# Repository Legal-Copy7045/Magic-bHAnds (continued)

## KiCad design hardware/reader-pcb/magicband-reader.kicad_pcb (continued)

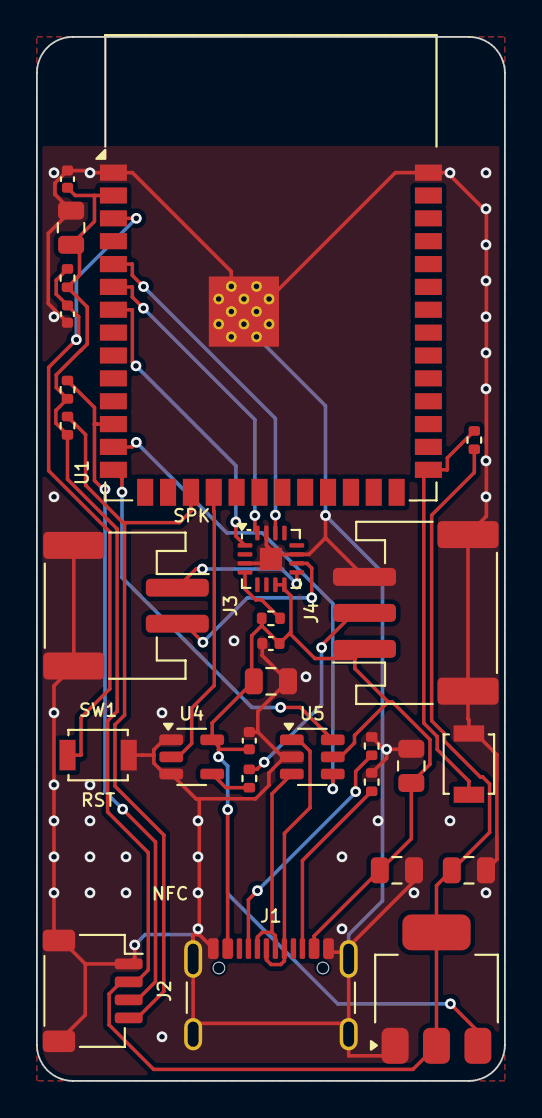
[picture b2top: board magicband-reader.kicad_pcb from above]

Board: 2 copper layers, 26.0 x 58.0 mm, 28 parts (0 on the bottom side), 22 nets.

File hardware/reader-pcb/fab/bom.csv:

Comment,Designator,Footprint,MPN,LCSC Part #
22uF,"C1,C5,C9",C_0805_2012Metric,CL21A226MAQNNNE,C45783
100nF,"C2,C7,C8",C_0402_1005Metric,CL05B104KO5NNNC,C1525
1uF,C3,C_0402_1005Metric,CL05A105KA5NQNC,C52923
10uF,"C4,C6",C_0805_2012Metric,CL21A106KAYNNNE,C15850
USB-C,J1,USB_C_Receptacle_GCT_USB4105-xx-A_16P_TopMnt_Horizontal,USB4105-GF-A,
NFC (Qwiic),J2,JST_SH_SM04B-SRSS-TB_1x04-1MP_P1.00mm_Horizontal,SM04B-SRSS-TB(LF)(SN),
Speaker,J3,JST_PH_S2B-PH-SM4-TB_1x02-1MP_P2.00mm_Horizontal,S2B-PH-SM4-TB(LF)(SN),
LEDs,J4,JST_PH_S3B-PH-SM4-TB_1x03-1MP_P2.00mm_Horizontal,S3B-PH-SM4-TB(LF)(SN),
10k,"R1,R2",R_0402_1005Metric,0402WGF1002TCE,C25744
5.1k,"R3,R4",R_0402_1005Metric,0402WGF5101TCE,C25905
1M,R5,R_0402_1005Metric,0402WGF1004TCE,C26083
330R,R6,R_0402_1005Metric,0402WGF3300TCE,C25104
4.7k,"R7,R8",R_0402_1005Metric,0402WGF4701TCE,C25900
RESET,SW1,SW_SPST_B3U-1000P,B3U-1000P,
BOOT,SW2,SW_SPST_B3U-1000P,B3U-1000P,
ESP32-S3-WROOM-1-N16R8,U1,ESP32-S3-WROOM-1,ESP32-S3-WROOM-1-N16R8,C2913202
AMS1117-3.3,U2,SOT-223-3_TabPin2,AMS1117-3.3,C6186
MAX98357A,U3,TQFN-16-1EP_3x3mm_P0.5mm_EP1.23x1.23mm,MAX98357AETE+T,C910544
74AHCT1G125,U4,SOT-23-5,SN74AHCT1G125DBVR,
USBLC6-2SC6,U5,SOT-23-6,USBLC6-2SC6,C7519

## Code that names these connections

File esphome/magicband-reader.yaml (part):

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# WAV/FLAC/MP3 under 5 MB each; see docs/reader.md.
i2s_audio:
  - id: i2s_out
    i2s_lrclk_pin: GPIO5   # MAX98357A LRC
    i2s_bclk_pin: GPIO6    # MAX98357A BCLK

speaker:
  - platform: i2s_audio
    id: spk
    i2s_audio_id: i2s_out
    i2s_dout_pin: GPIO7
    dac_type: external
    channel: mono

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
